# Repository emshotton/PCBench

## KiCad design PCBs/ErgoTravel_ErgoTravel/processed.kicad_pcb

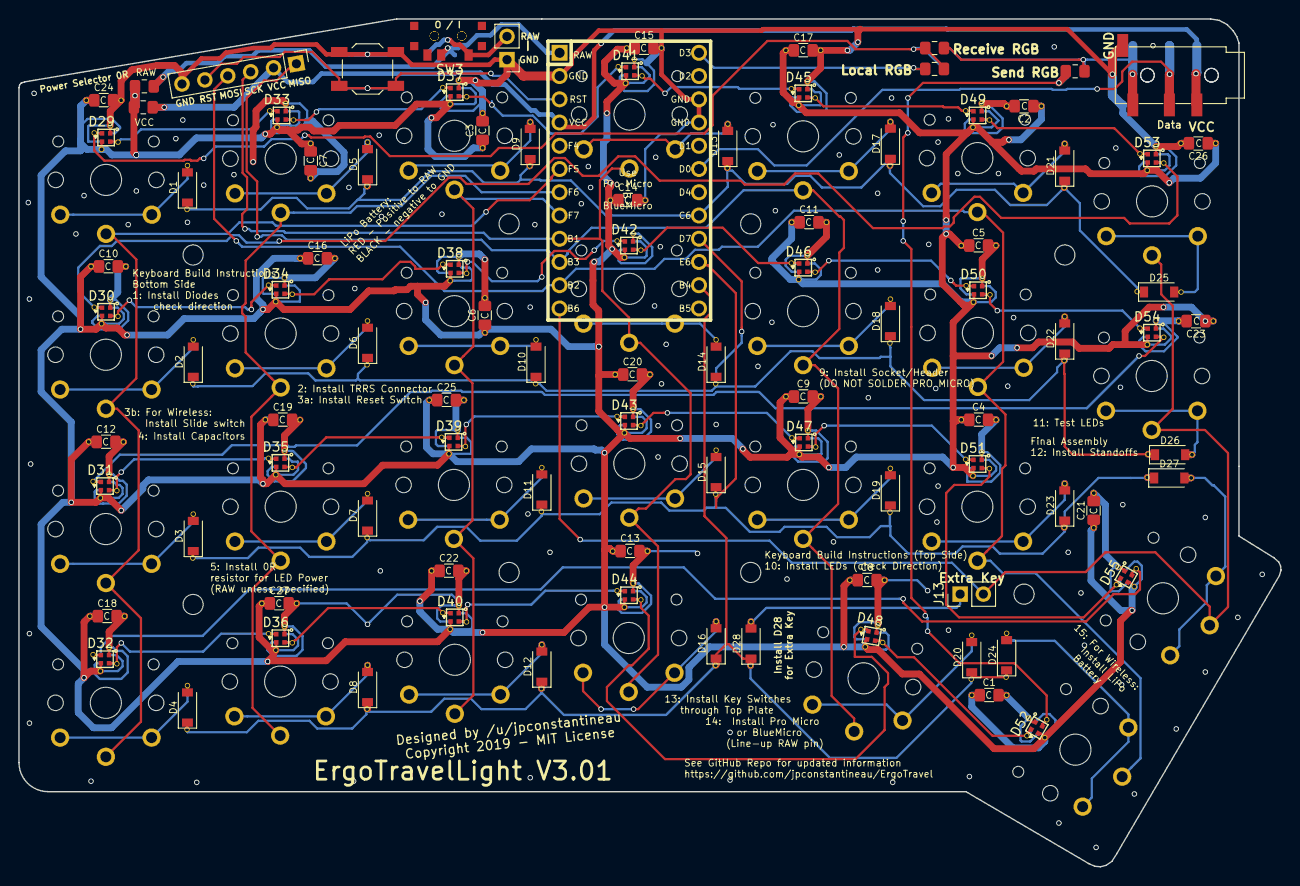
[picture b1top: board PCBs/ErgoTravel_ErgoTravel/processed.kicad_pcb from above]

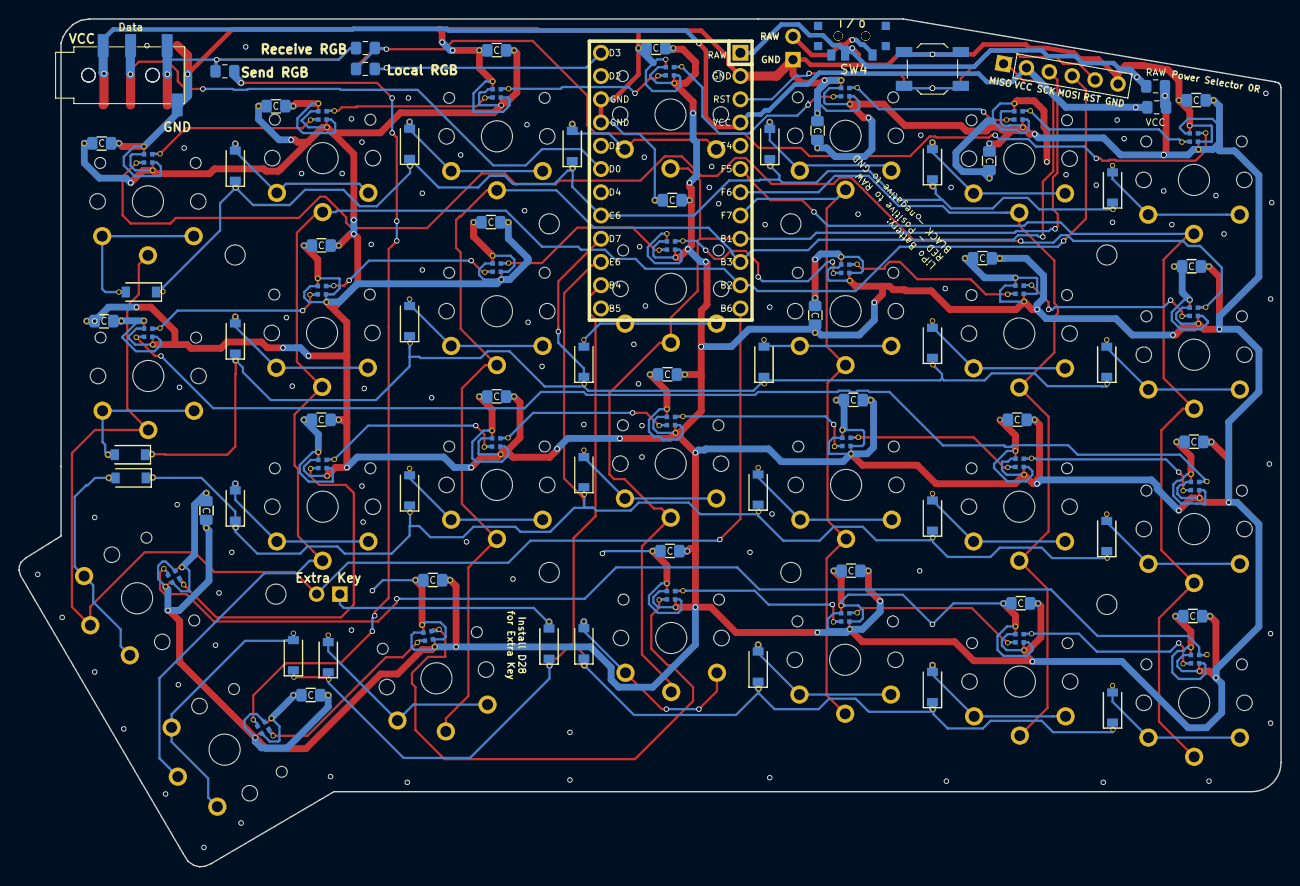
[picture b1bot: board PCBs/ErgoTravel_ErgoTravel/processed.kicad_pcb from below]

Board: 2 copper layers, 137.9 x 92.7 mm, 137 parts (8 on the bottom side), 76 nets.

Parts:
C1, C2, C3, C4, C5, C6, C7, C8, C9, C10, C11, C12, C13, C14, C15, C16, C17, C18, C19, C20, C21, C22, C23, C24, C25, C26, C27: 100nF; C_0805_2012Metric_Pad1.15x1.40mm_HandSolder-double-sided
D1, D2, D3, D4, D5, D6, D7, D8, D9, D10, D11, D12, D13, D14, D15, D16, D17, D18, D19, D20, D21, D22, D23, D24, D25, D26, D27, D28: D; D_SOD-123-double-sided
D29, D30, D31, D32, D33, D34, D35, D36, D37, D38, D39, D40, D41, D42, D43, D44, D45, D46, D47, D48, D49, D50, D51, D52, D53, D54, D55: SK6812-EC1515; SK6812-EC1515-double-sided
J2, J3: Audio-Jack-4; PJ320D_3.5mm_Jack
J4: Conn_01x06; ICSP-Header
J5, J6, J7, J8, J9, J10, J11, J12: Conn_01x01; MountingHole_2.2mm_M2_DIN965
J13, J14: Conn_01x02; Pin_Header_Straight_1x02_Pitch2.54mm
K1, K2, K3, K4, K5, K6, K7, K8, K9, K10, K11, K12, K13, K14, K15, K16, K17, K18, K19, K20, K21, K22, K23, K24, K26, K27, K28: KEYSW; Kailh-PG1350-1u-reversible_SMDLED
R1, R2, R3, R4, R5, R6, R7, R8, R9, R10: 0R; R_0805_2012Metric_Pad1.15x1.40mm_HandSolder
SW1, SW2: SW_PUSH; SW_TACT_ALPS_SKQGABE010
SW3, SW4: SW_SPDT; SPDT_C128955
U1: ProMicro; Pro_Micro

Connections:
/RAW: R7.2, R9.2, SW3.2, SW4.2, U1.1
GND: C1.2, C2.2, C3.2, C4.2, C5.2, C6.2, C7.2, C8.2, C9.2, C10.2, C11.2, C12.2, C13.2, C14.2, C15.2, C16.2, C17.2, C18.2, C19.2, C20.2, C21.2, C22.2, C23.2, C24.2, C25.2, C26.2, C27.2, D29.4, D30.4, D31.4, D32.4, D33.4, D34.4, D35.4, D36.4, D37.4, D38.4, D39.4, D40.4, D41.4, D42.4, D43.4, D44.4, D45.4, D46.4, D47.4, D48.4, D49.4, D50.4, D51.4, D52.4, D53.4, D54.4, D55.4, J2.4, J3.4, J4.6, J14.1, SW1.2, SW2.2, U1.2, U1.15, U1.16
MISO: J4.1, K17.1, K18.1, K19.1, K20.1, U1.10
MOSI: J4.4, K21.1, K22.1, K23.1, K24.1, U1.11
unnamed: D1.2, K1.2
unnamed: D2.2, K2.2
unnamed: D3.2, K3.2
unnamed: D4.2, K4.2
unnamed: D5.2, K5.2
unnamed: D6.2, K6.2
unnamed: D7.2, K7.2
unnamed: D8.2, K8.2
unnamed: D9.2, K9.2
unnamed: D10.2, K10.2
unnamed: D11.2, K11.2
unnamed: D12.2, K12.2
unnamed: D13.2, K13.2
unnamed: D14.2, K14.2
unnamed: D15.2, K15.2
unnamed: D16.2, K16.2
unnamed: D17.2, K17.2
unnamed: D18.2, K18.2
unnamed: D19.2, K19.2
unnamed: D20.2, K20.2
unnamed: D21.2, K21.2
unnamed: D22.2, K22.2
unnamed: D23.2, K23.2
unnamed: D24.2, K24.2
unnamed: D25.2, K26.2
unnamed: D26.2, K27.2
unnamed: D27.2, K28.2
unnamed: D28.2, J13.1
unnamed: D29.3, D33.1
unnamed: D30.1, D53.3
unnamed: D30.3, D34.1
unnamed: D31.1, D54.3
unnamed: D31.3, D35.1
unnamed: D32.1, D55.3
unnamed: D32.3, D36.1
unnamed: D33.3, D37.1
unnamed: D34.3, D38.1
unnamed: D35.3, D39.1
unnamed: D36.3, D40.1
unnamed: D37.3, D41.1
unnamed: D38.3, D42.1
unnamed: D39.3, D43.1
unnamed: D40.3, D44.1
unnamed: D41.3, D45.1
unnamed: D42.3, D46.1
unnamed: D43.3, D47.1
unnamed: D44.3, D48.1
unnamed: D45.3, D49.1
unnamed: D46.3, D50.1
unnamed: D47.3, D51.1
unnamed: D48.3, D52.1
unnamed: D49.3, D53.1
unnamed: D50.3, D54.1
unnamed: D51.3, D55.1
unnamed: J14.2, SW3.1, SW4.1
RESET: J4.5, SW1.1, SW2.1, U1.3
RGB: J2.1, J3.1, R3.2, R4.2, R5.1, R6.1
RGBData: D29.1, R1.1, R2.1, R3.1, R4.1
RGBOut: D52.3, R5.2, R6.2
RGBPM: R1.2, R2.2, U1.13
RGBPower: C1.1, C2.1, C3.1, C4.1, C5.1, C6.1, C7.1, C8.1, C9.1, C10.1, C11.1, C12.1, C13.1, C14.1, C15.1, C16.1, C17.1, C18.1, C19.1, C20.1, C21.1, C22.1, C23.1, C24.1, C25.1, C26.1, C27.1, D29.2, D30.2, D31.2, D32.2, D33.2, D34.2, D35.2, D36.2, D37.2, D38.2, D39.2, D40.2, D41.2, D42.2, D43.2, D44.2, D45.2, D46.2, D47.2, D48.2, D49.2, D50.2, D51.2, D52.2, D53.2, D54.2, D55.2, R7.1, R8.1, R9.1, R10.1
SCK: J4.3, K13.1, K14.1, K15.1, K16.1, U1.9
VCC: J2.3, J3.3, J4.2, R8.2, R10.2, U1.4
col0: K1.1, K2.1, K3.1, K4.1, U1.6
col1: K5.1, K6.1, K7.1, K8.1, U1.7
col2: K9.1, K10.1, K11.1, K12.1, U1.8
col6: J13.2, K26.1, K27.1, K28.1, U1.12
row0: D1.1, D5.1, D9.1, D13.1, D17.1, D21.1, D25.1, U1.20
row1: D2.1, D6.1, D10.1, D14.1, D18.1, D22.1, D26.1, U1.21
row2: D3.1, D7.1, D11.1, D15.1, D19.1, D23.1, D27.1, U1.22
row3: D4.1, D8.1, D12.1, D16.1, D20.1, D24.1, D28.1, U1.23
scl: J2.2, J3.2, U1.18

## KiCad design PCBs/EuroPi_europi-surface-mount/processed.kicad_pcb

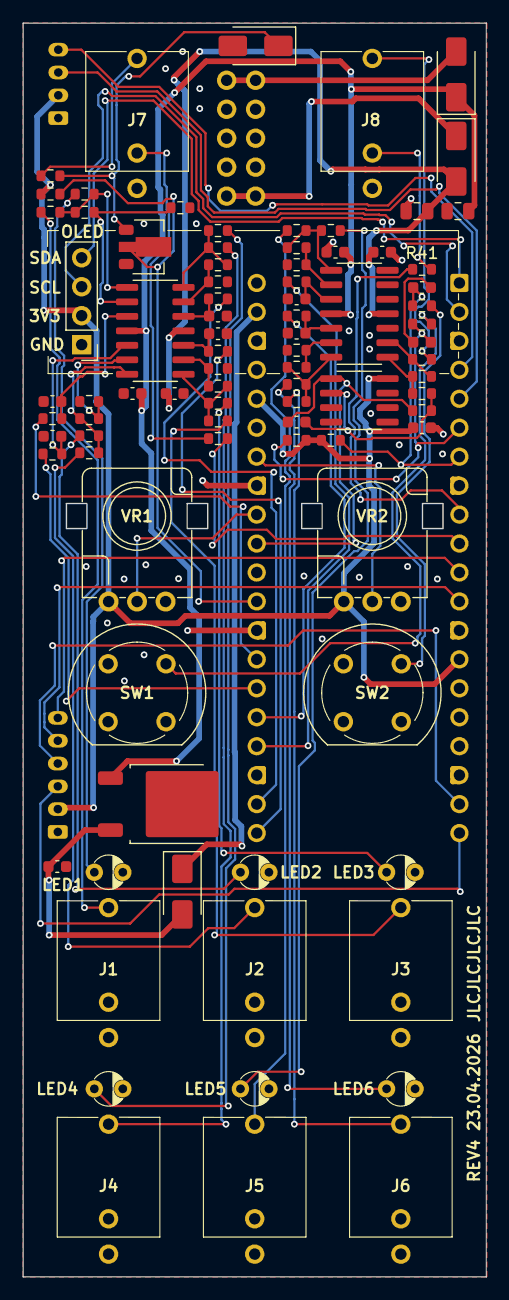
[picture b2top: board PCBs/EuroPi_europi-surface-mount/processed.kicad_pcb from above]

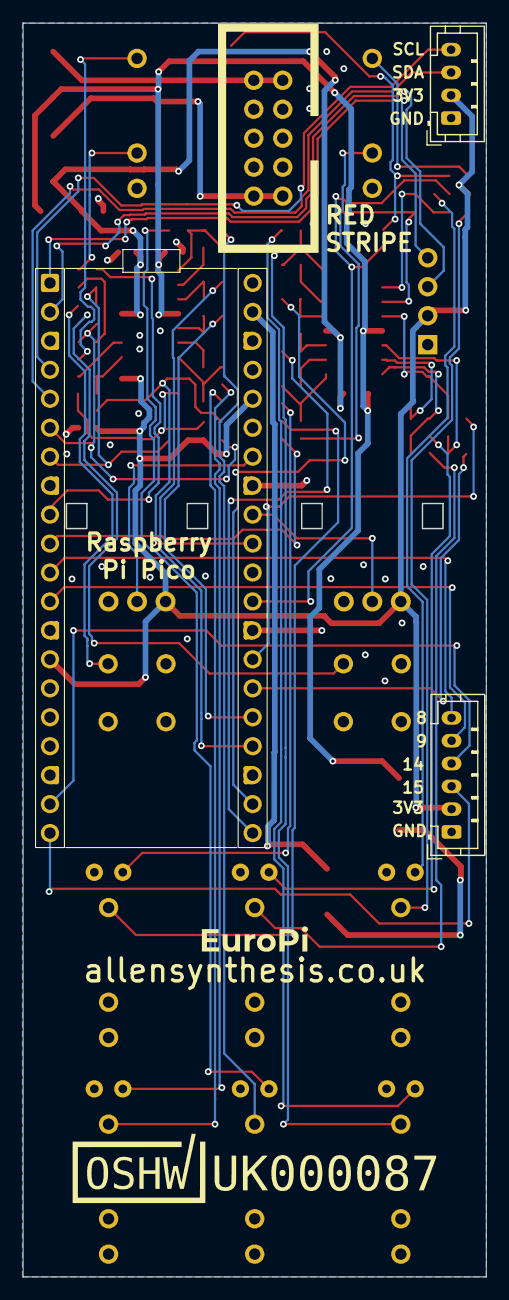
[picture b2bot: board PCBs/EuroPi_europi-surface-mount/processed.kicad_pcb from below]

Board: 2 copper layers, 40.6 x 110.0 mm, 91 parts (4 on the bottom side), 70 nets.

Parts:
C1, C2: 10uF; C_0805_2012Metric
C3: 1uF; C_0603_1608Metric
C4, C5, C6, C7, C9, C10, C11, C12, C13, C14, C16, C17, C18: 100nF; C_0603_1608Metric
C15: 1nF; C_0603_1608Metric
D1, D2, D3, D5: D; D_SMA
J1: Conn_02x05_Odd_Even; power-header-10-pin-unlabelled
J2: Conn_01x04_Pin; PinHeader_1x04_P2.54mm_Vertical
J3: Output 1 Jack; jack-thonkiconn-mono
J4: Output 4 Jack; jack-thonkiconn-mono
J5: Analogue Input Jack; jack-thonkiconn-mono
J6: Output 2 Jack; jack-thonkiconn-mono
J7: Output 5 Jack; jack-thonkiconn-mono
J8: Digital Input Jack; jack-thonkiconn-mono
J9: Output 3 Jack; jack-thonkiconn-mono
J10: Output 6 Jack; jack-thonkiconn-mono
J11: Conn_01x04_Pin; JST_PH_B4B-PH-K_1x04_P2.00mm_Vertical
J12: Conn_01x04_Pin; JST_PH_B6B-PH-K_1x06_P2.00mm_Vertical
LED1, LED2, LED3, LED4, LED5, LED6: LED; led-3mm
Q1: 2N2222; SOT-89-3
R1, R2, R3, R4, R13, R14, R16, R17, R26, R27, R29, R30, R38, R39: 1K; R_0603_1608Metric
R5, R6, R40, R41, R42: 10K; R_0603_1608Metric
R7, R8, R15, R19, R20, R31, R32, R35: 100K; R_0603_1608Metric
R9, R10, R21, R22, R33, R34: 220K; R_0603_1608Metric
R11, R12, R24, R25, R36, R37: 5K1; R_0603_1608Metric
R18, R23, R28: 22K; R_0603_1608Metric
SW1, SW2: SW_Push; switch-momentary-c&k
U2: PICO_RP2040; raspberry-pi-pico
U3, U4: TL074; SOIC-14_3.9x8.7mm_P1.27mm
U5: MCP6002-xSN; SOIC-8_3.9x4.9mm_P1.27mm
U6: L7805; TO-252-2
VR1: KNOB 1; potentiometer-9mm
VR2: KNOB 2; potentiometer-9mm

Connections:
+3.3V: C18.1, J2.2, J11.2, J12.2, R5.2, R6.2, R40.1, U2.14 (GP10), U2.36 (3V3), U5.8 (V+), VR1.1, VR2.1
+5V: C3.1, D2.2 (A), U6.3 (OUT)
+12V: C1.1, C4.1, C6.1, D5.1 (K), U3.4 (V+), U4.4 (V+), U6.1 (IN)
-12V: C2.2, C5.2, C7.2, D1.2 (A), U3.11 (V-), U4.11 (V-)
AIN_DETECT: R41.1, U2.9 (GP6)
ANALOGUE_IN: C15.2, R28.2, U2.31 (GP26), U5.1
BUTTON_1: C9.1, R1.1, R5.1, U2.6 (GP4)
BUTTON_2: C10.1, R2.1, R6.1, U2.7 (GP5)
DIGITAL_IN: Q1.2 (C), R40.2, U2.29 (GP22)
DIN_DETECT: R42.1, U2.10 (GP7)
GND: C1.2, C2.1, C3.2, C4.2, C5.1, C6.2, C7.1, C9.2, C10.2, C11.2, C12.2, C13.2, C14.2, C16.2, C17.2, C18.2, D3.2 (A), J1.3, J1.4, J1.5, J1.6, J1.7, J1.8, J2.1, J3.1 (E), J4.1 (E), J5.1 (E), J6.1 (E), J7.1 (E), J8.1 (E), J9.1 (E), J10.1 (E), J11.1, J12.1, LED1.1 (K), LED2.1 (K), LED3.1 (K), LED4.1 (K), LED5.1 (K), LED6.1 (K), Q1.3 (E), R7.2, R8.2, R19.2, R20.2, R31.2, R32.2, SW1.1, SW2.1, U2.3 (GND), U2.8 (GND), U2.13 (GND), U2.18 (GND), U2.23 (GND), U2.28 (GND), U2.33 (GND), U2.38 (GND), U4.10 (+), U5.3 (+), U5.4 (V-), U6.2 (GND), VR1.3, VR2.3
GP8: J12.6, U2.11 (GP8)
GP9: J12.5, U2.12 (GP9)
GP14: J12.4, U2.19 (GP14)
GP15: J12.3, U2.20 (GP15)
I2C_SCL: J11.3, U2.5 (GP3)
I2C_SDA: J11.4, U2.4 (GP2)
KNOB_1: U2.32 (GP27), VR1.2
KNOB_2: U2.34 (GP28), VR2.2
unnamed: D1.1 (K), J1.1, J1.2
unnamed: D2.1 (K), U2.39 (VSYS)
unnamed: D3.1 (K), Q1.1 (B), R35.2
unnamed: D5.2 (A), J1.9, J1.10
unnamed: J3.3 (T), R13.2
unnamed: J4.3 (T), R14.2
unnamed: J5.3 (T), R15.1
unnamed: J5.2 (TN), R41.2
unnamed: J6.3 (T), R26.2
unnamed: J7.3 (T), R27.2
unnamed: J8.3 (T), R35.1
unnamed: J8.2 (TN), R42.2
unnamed: J9.3 (T), R38.2
unnamed: J10.3 (T), R39.2
unnamed: LED1.2 (A), R11.1
unnamed: LED2.2 (A), R12.1
unnamed: LED3.2 (A), R24.1
unnamed: LED4.2 (A), R25.1
unnamed: LED5.2 (A), R36.1
unnamed: LED6.2 (A), R37.1
unnamed: R1.2, SW1.2
unnamed: R2.2, SW2.2
unnamed: R10.1, R12.2, R14.1, U3.14
unnamed: R9.1, R11.2, R13.1, U3.1
unnamed: R18.2, R23.1, U4.8
unnamed: R21.1, R24.2, R26.1, U3.7
unnamed: R22.1, R25.2, R27.1, U4.1
unnamed: R33.1, R36.2, R38.1, U3.8
unnamed: R34.1, R37.2, R39.1, U4.7
unnamed: C11.1, R3.1, U3.3 (+)
unnamed: R7.1, R9.2, U3.2 (-)
unnamed: C13.1, R16.1, U3.5 (+)
unnamed: R19.1, R21.2, U3.6 (-)
unnamed: C16.1, R29.1, U3.10 (+)
unnamed: R31.1, R33.2, U3.9 (-)
unnamed: C12.1, R4.1, U3.12 (+)
unnamed: R8.1, R10.2, U3.13 (-)
unnamed: C14.1, R17.1, U4.3 (+)
unnamed: R20.1, R22.2, U4.2 (-)
unnamed: C17.1, R30.1, U4.5 (+)
unnamed: R32.1, R34.2, U4.6 (-)
unnamed: R15.2, R18.1, U4.9 (-)
unnamed: C15.1, R23.2, R28.1, U5.2 (-)
OLED_SCL: J2.3, U2.2 (GP1)
OLED_SDA: J2.4, U2.1 (GP0)
OUT_1: R3.2, U2.27 (GP21)
OUT_2: R16.2, U2.26 (GP20)
OUT_3: R29.2, U2.21 (GP16)
OUT_4: R4.2, U2.22 (GP17)
OUT_5: R17.2, U2.24 (GP18)
OUT_6: R30.2, U2.25 (GP19)

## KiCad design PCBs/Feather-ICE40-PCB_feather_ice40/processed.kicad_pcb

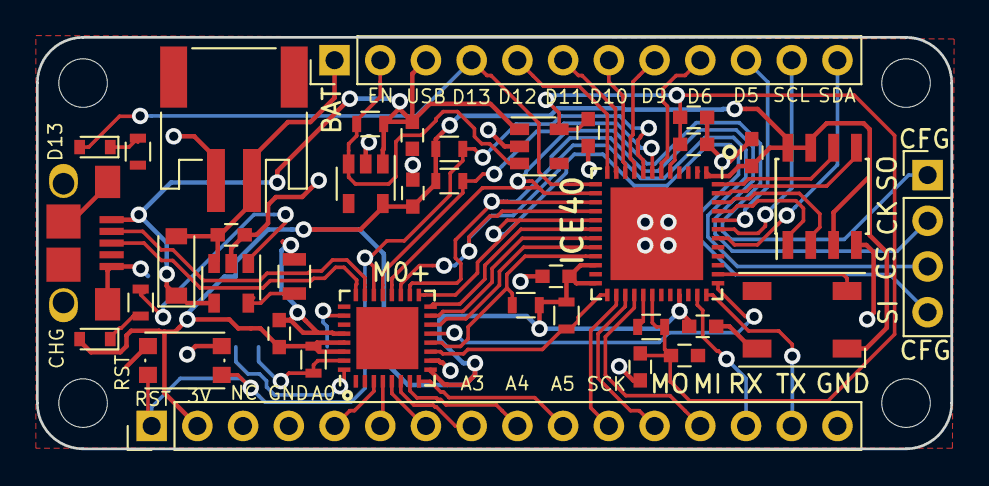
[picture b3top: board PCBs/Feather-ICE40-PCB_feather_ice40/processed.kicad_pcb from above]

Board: 2 copper layers, 50.8 x 22.9 mm, 43 parts (1 on the bottom side), 53 nets.

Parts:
C1, C2, C4, C5, C8: 0.1uF; C_0603
C6, C14, C16, C19, C20: 10uF; C_0603
C7, C18: 1uF; C_0603
D1: MBR120; D_SOD-123
D2: Yellow; D_0603
D3: Red; D_0603
D4: Neopixel_THT; LED_WS2812B-PLCC4
J1: USB_OTG; Mini-USB-B-OshPark
J2: CONN_01X02; JST_PH_S2B-PH-SM4-TB_02x2.00mm_Angled
J3, J4, J5, J6: CONN_01X01; MountingHole_2.7mm_M2.5
J7: CONN_02X05; Pin_Header_Straight_2x05_Pitch1.27mm_SMD
J8: Conn_01x04; Pin_Header_Straight_1x04_Pitch2.54mm
J9: FeatherBottom; Pin_Header_Straight_1x16_Pitch2.54mm
J10: FeatherTop; Pin_Header_Straight_1x12_Pitch2.54mm
R1, R3: 10k; R_0603
R2: 100; R_0603
R4: 100k; R_0603
R5, R8, R10: 1k; R_0603
R6, R7: 4.7k; R_0603
R9: 10k; R_0805
SW1: SW_SPST; SW_SPST_KMR2
U1: ICE40UP5K-SG48; QFN-48-1EP_7x7mm_Pitch0.5mm
U2: IS25LPXXX; SOIC-8_3.9x4.9mm_Pitch1.27mm
U3: SPX3819M5-L-3-3/TR; SOT-23-5
U4: SPX3819M5-L-1-2/TR; SOT-23-5
U5: SAMD21E; QFN-32-1EP_5x5mm_Pitch0.5mm
U6: MCP73831; SOT-23-5

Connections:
+1V2: C5.1, C6.1, C7.1, C8.1, C16.1, R2.1, U1.5, U1.30, U4.5
+3V3: C1.1, C2.1, C4.1, C14.1, C18.2, D2.2, D4.3, J7.1, J9.2, R1.1, R3.1, R6.1, R7.1, R10.1, U1.1, U1.22, U1.24, U1.33, U2.3, U2.7, U2.8, U3.5, U5.9, U5.29, U5.30
+5V: C19.1, D1.1, J1.1, J10.3, R4.1, U3.1, U4.1, U6.4
+BATT: C20.1, D1.2, J2.1, J10.1, U6.3
/A0: J9.5, U5.3
/A1: J9.6, U5.4
/A2: J9.7, U5.5
/A3: J9.8, U5.6
/A4: J9.9, U5.7
/A5: J9.10, U5.8
/CHARGE: R5.2, U6.1
/D5: J10.10, U1.44
/D6: J10.9, U1.6
/D9: J10.8, U1.9
/D10: J10.7, U1.10
/D11: J10.6, U1.11
/D12: J10.5, U1.12
/D13: D3.2, J10.4, U1.13
/EN: J10.2, R4.2, U3.3, U4.3
/GCLK4: U1.37, U5.13
/GCLK5: U1.20, U5.14
/M0RX: U1.18, U5.16
/M0TX: U1.19, U5.15
/M0_RST: J7.10, U5.26
/M0_SWCLK: J7.4, R10.2, U5.31
/M0_SWDIO: J7.2, U5.32
/NEOPIX: D4.4, U1.38
/USB_D+: J1.3, U5.24
/USB_D-: J1.2, U5.23
/cdone: R3.2, U1.7, U5.21
/configMISO: J8.1, U1.14, U5.20
/configMOSI: J8.4, U1.17, U5.17
/configSCK: J8.2, U1.15, U5.18
/configSS: J8.3, U1.16, U5.19
/flashMISO: U1.46, U2.2
/flashMOSI: U1.47, U2.5
/flashSCK: U1.48, U2.6
/flashSS: U1.45, U2.1
/iceMISO: J9.13, U1.28
/iceMOSI: J9.12, U1.27
/iceRX: J9.14, U1.35
/iceReset: J9.1, R1.2, SW1.2, U1.8, U5.22
/iceSCK: J9.11, U1.26
/iceSCL: J10.11, U1.43
/iceSDA: J10.12, U1.42
/iceTX: J9.15, U1.36
/sharedSCL: R6.2, U1.21, U5.12
/sharedSDA: R7.2, U1.25, U5.11
GND: C1.2, C2.2, C4.2, C5.2, C6.2, C7.2, C8.2, C14.2, C16.2, C18.1, C19.2, C20.2, D4.2, J1.5, J1.6, J2.2, J7.3, J7.5, J9.4, J9.16, R8.2, R9.2, SW1.1, U1.49, U2.4, U3.2, U4.2, U5.10, U5.28, U6.2
unnamed: D2.1, R5.1
unnamed: D3.1, R8.1
unnamed: R2.2, U1.29
unnamed: R9.1, U6.5

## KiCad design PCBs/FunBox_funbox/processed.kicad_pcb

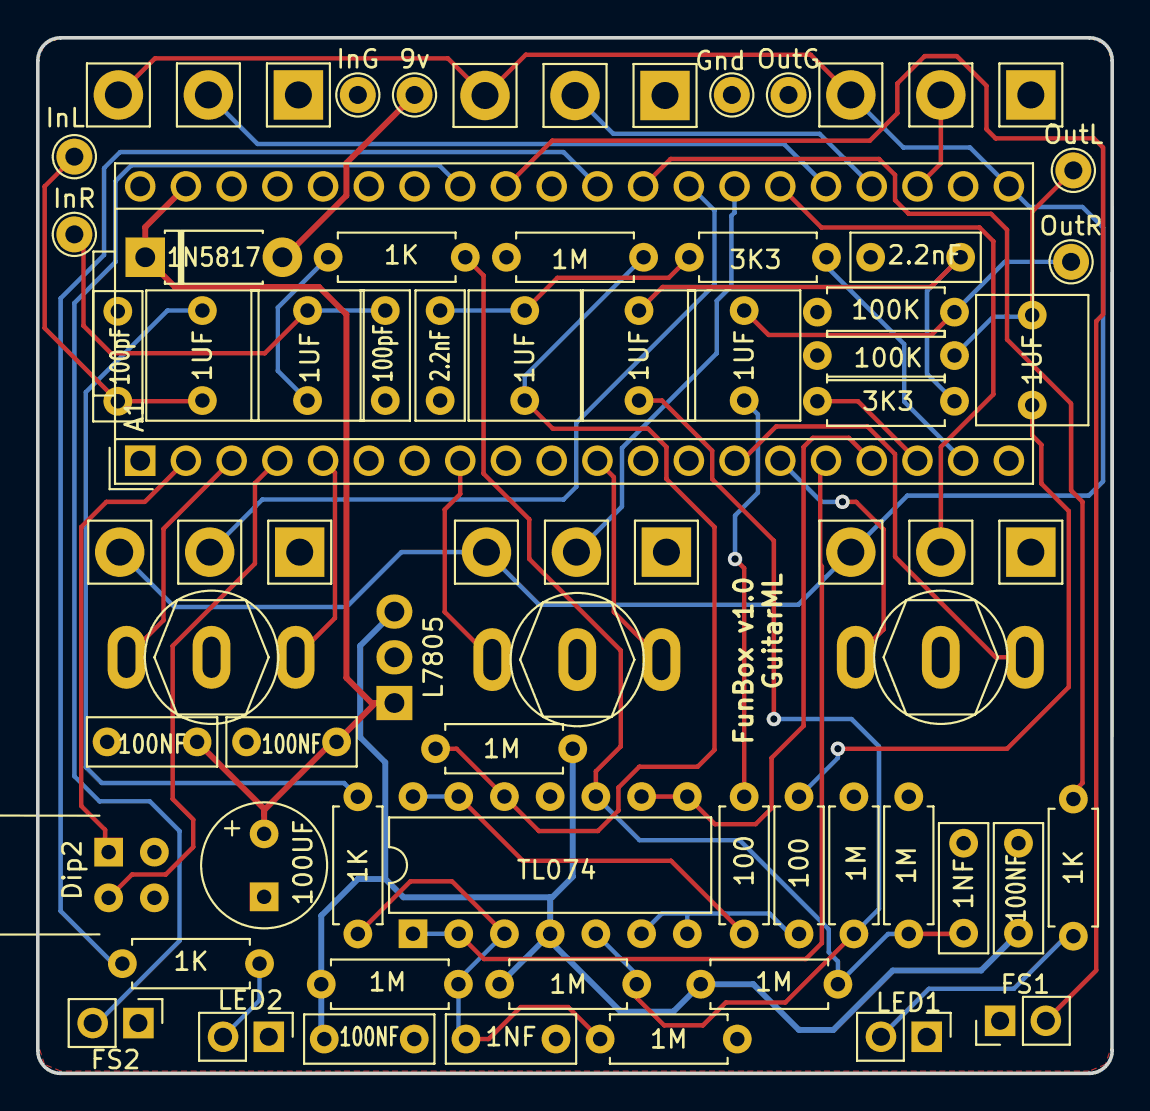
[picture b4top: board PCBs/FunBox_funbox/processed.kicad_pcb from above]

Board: 2 copper layers, 59.7 x 57.5 mm, 61 parts (0 on the bottom side), 45 nets.

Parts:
9v: TestPoint_THTPad_D2.0mm_Drill1.0mm
A1: Electrosmith_Daisy_Seed_Rev4; Electrosmith_Daisy_Seed
C1, C4, C5, C14, C15, C17: 1UF; C_Rect_L7.0mm_W6.0mm_P5.00mm
C2, C11: 100pF; C_Rect_L7.0mm_W2.5mm_P5.00mm
C3, C16: 1NF; C_Rect_L7.0mm_W2.5mm_P5.00mm
C6: 100UF; CP_Radial_D8.0mm_P3.50mm
C7, C8, C9, C10: 100NF; C_Rect_L7.0mm_W2.5mm_P5.00mm
C12, C13: 2.2nF; C_Rect_L7.0mm_W2.5mm_P5.00mm
D1: 1N5817; D_DO-41_SOD81_P7.62mm_Horizontal
Dip2: DS03-254-02BE; DS03-254-02BE-dip2
FS1: Foot_Switch_1; PinHeader_1x02_P2.54mm_Vertical
FS2: Foot_Switch_2; PinHeader_1x02_P2.54mm_Vertical
Gnd: TestPoint_THTPad_D2.0mm_Drill1.0mm
InG: TestPoint_THTPad_D2.0mm_Drill1.0mm
InL: TestPoint_THTPad_D2.0mm_Drill1.0mm
InR: TestPoint_THTPad_D2.0mm_Drill1.0mm
LED1: LED_1; PinHeader_1x02_P2.54mm_Vertical
LED2: LED_2; PinHeader_1x02_P2.54mm_Vertical
OutG: TestPoint_THTPad_D2.0mm_Drill1.0mm
OutL: TestPoint_THTPad_D2.0mm_Drill1.0mm
OutR: TestPoint_THTPad_D2.0mm_Drill1.0mm
POT1, POT2, POT3, POT4, POT5, POT6: 10K; Pot_RightAngle_LongPin_16mm
R1, R2, R5, R6, R13, R14, R15, R16: 1M; R_Axial_DIN0207_L6.3mm_D2.5mm_P7.62mm_Horizontal
R3, R8, R9, R12: 1K; R_Axial_DIN0207_L6.3mm_D2.5mm_P7.62mm_Horizontal
R4, R17: 100; R_Axial_DIN0207_L6.3mm_D2.5mm_P7.62mm_Horizontal
R7, R18: 100K; R_Axial_DIN0207_L6.3mm_D2.5mm_P7.62mm_Horizontal
R10, R11: 3K3; R_Axial_DIN0207_L6.3mm_D2.5mm_P7.62mm_Horizontal
SW1, SW2, SW3: SW_SPDT; SW_Toggle_SPDT_lugs
U1: TL074; DIP-14_W7.62mm
U2: L7805; TO-220-3_Vertical

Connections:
3V3_A: A1.21 (3V3_A), POT1.3, POT2.3, POT3.3, POT4.3, POT5.3, POT6.3
5V: C9.2, C10.2, R2.1, R5.1, R13.1, R15.1, U1.4 (V+), U2.3 (OUT)
AUDIO_IN_BUFFER_LEFT: A1.16 (AUDIO_IN_1), U1.1, U1.2 (-)
AUDIO_IN_BUFFER_RIGHT: A1.17 (AUDIO_IN_2), U1.8, U1.9 (-)
AUDIO_OUT_BUFFER_LEFT: A1.18 (AUDIO_OUT_1), R11.1
AUDIO_OUT_BUFFER_RIGHT: A1.19 (AUDIO_OUT_2), R10.1
DIP1: A1.2 (SD_DATA_3), Dip2.1A
DIP2: A1.4 (SD_DATA_1), Dip2.2A
FOOT_SWITCH_1: A1.32 (SAI2_SD_B), FS1.2
FOOT_SWITCH_2: A1.33 (SAI2_SD_A), FS2.2
GND: A1.20 (AGND), A1.40 (DGND), C2.2, C3.1, C6.1, C7.1, C8.1, C9.1, C10.1, C11.2, C12.2, C13.2, C16.1, Dip2.1B, Dip2.2B, FS1.1, FS2.1, Gnd.1, InG.1, LED1.1 (K), LED2.1 (K), OutG.1, POT1.1, POT2.1, POT3.1, POT4.1, POT5.1, POT6.1, R1.2, R6.2, R7.1, R14.2, R16.2, R18.1, SW1.2 (B), SW2.2 (B), SW3.2 (B), U1.11 (V-), U2.2 (GND)
LED_1: A1.29 (DAC_OUT2), R8.2
LED_2: A1.30 (DAC_OUT1), R9.2
unnamed: 9v.1, D1.2 (A)
unnamed: C1.2, R3.1
unnamed: C5.2, R4.2
unnamed: C4.1, C12.1, R11.2
unnamed: C13.1, C15.1, R10.2
unnamed: C14.2, R12.1
unnamed: C17.2, R17.2
unnamed: C1.1, C2.1, InL.1
unnamed: C11.1, C14.1, InR.1
unnamed: LED1.2 (A), R8.1
unnamed: LED2.2 (A), R9.1
unnamed: C5.1, OutL.1, R7.2
unnamed: C17.1, OutR.1, R18.2
unnamed: C3.2, R1.1, R2.2, R3.2, U1.3 (+)
unnamed: C4.2, R5.2, R6.1, U1.5 (+)
unnamed: R4.1, U1.6 (-), U1.7
unnamed: C16.2, R12.2, R15.2, R16.1, U1.10 (+)
unnamed: C15.2, R13.2, R14.1, U1.12 (+)
unnamed: R17.1, U1.13 (-), U1.14
POT_1: A1.23 (ADC_1), POT1.2
POT_2: A1.24 (ADC_2), POT2.2
POT_3: A1.25 (ADC_3), POT3.2
POT_4: A1.26 (ADC_4), POT4.2
POT_5: A1.27 (ADC_5), POT5.2
POT_6: A1.28 (ADC_6), POT6.2
SW1_LEFT: A1.15 (USART1_RX), SW1.3 (C)
SW1_RIGHT: A1.14 (USART1_TX), SW1.1 (A)
SW2_LEFT: A1.8 (SPI1_CS), SW2.3 (C)
SW2_RIGHT: A1.11 (SPI1_PICO), SW2.1 (A)
SW3_LEFT: A1.3 (SD_DATA_2), SW3.3 (C)
SW3_RIGHT: A1.5 (SD_DATA_0), SW3.1 (A)
VCC: A1.39 (VIN), C6.2, C7.2, C8.2, D1.1 (K), U2.1 (IN)

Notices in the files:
PCBs/ErgoTravel_ErgoTravel/processed.kicad_pcb:
Copyright 2019 - MIT License
